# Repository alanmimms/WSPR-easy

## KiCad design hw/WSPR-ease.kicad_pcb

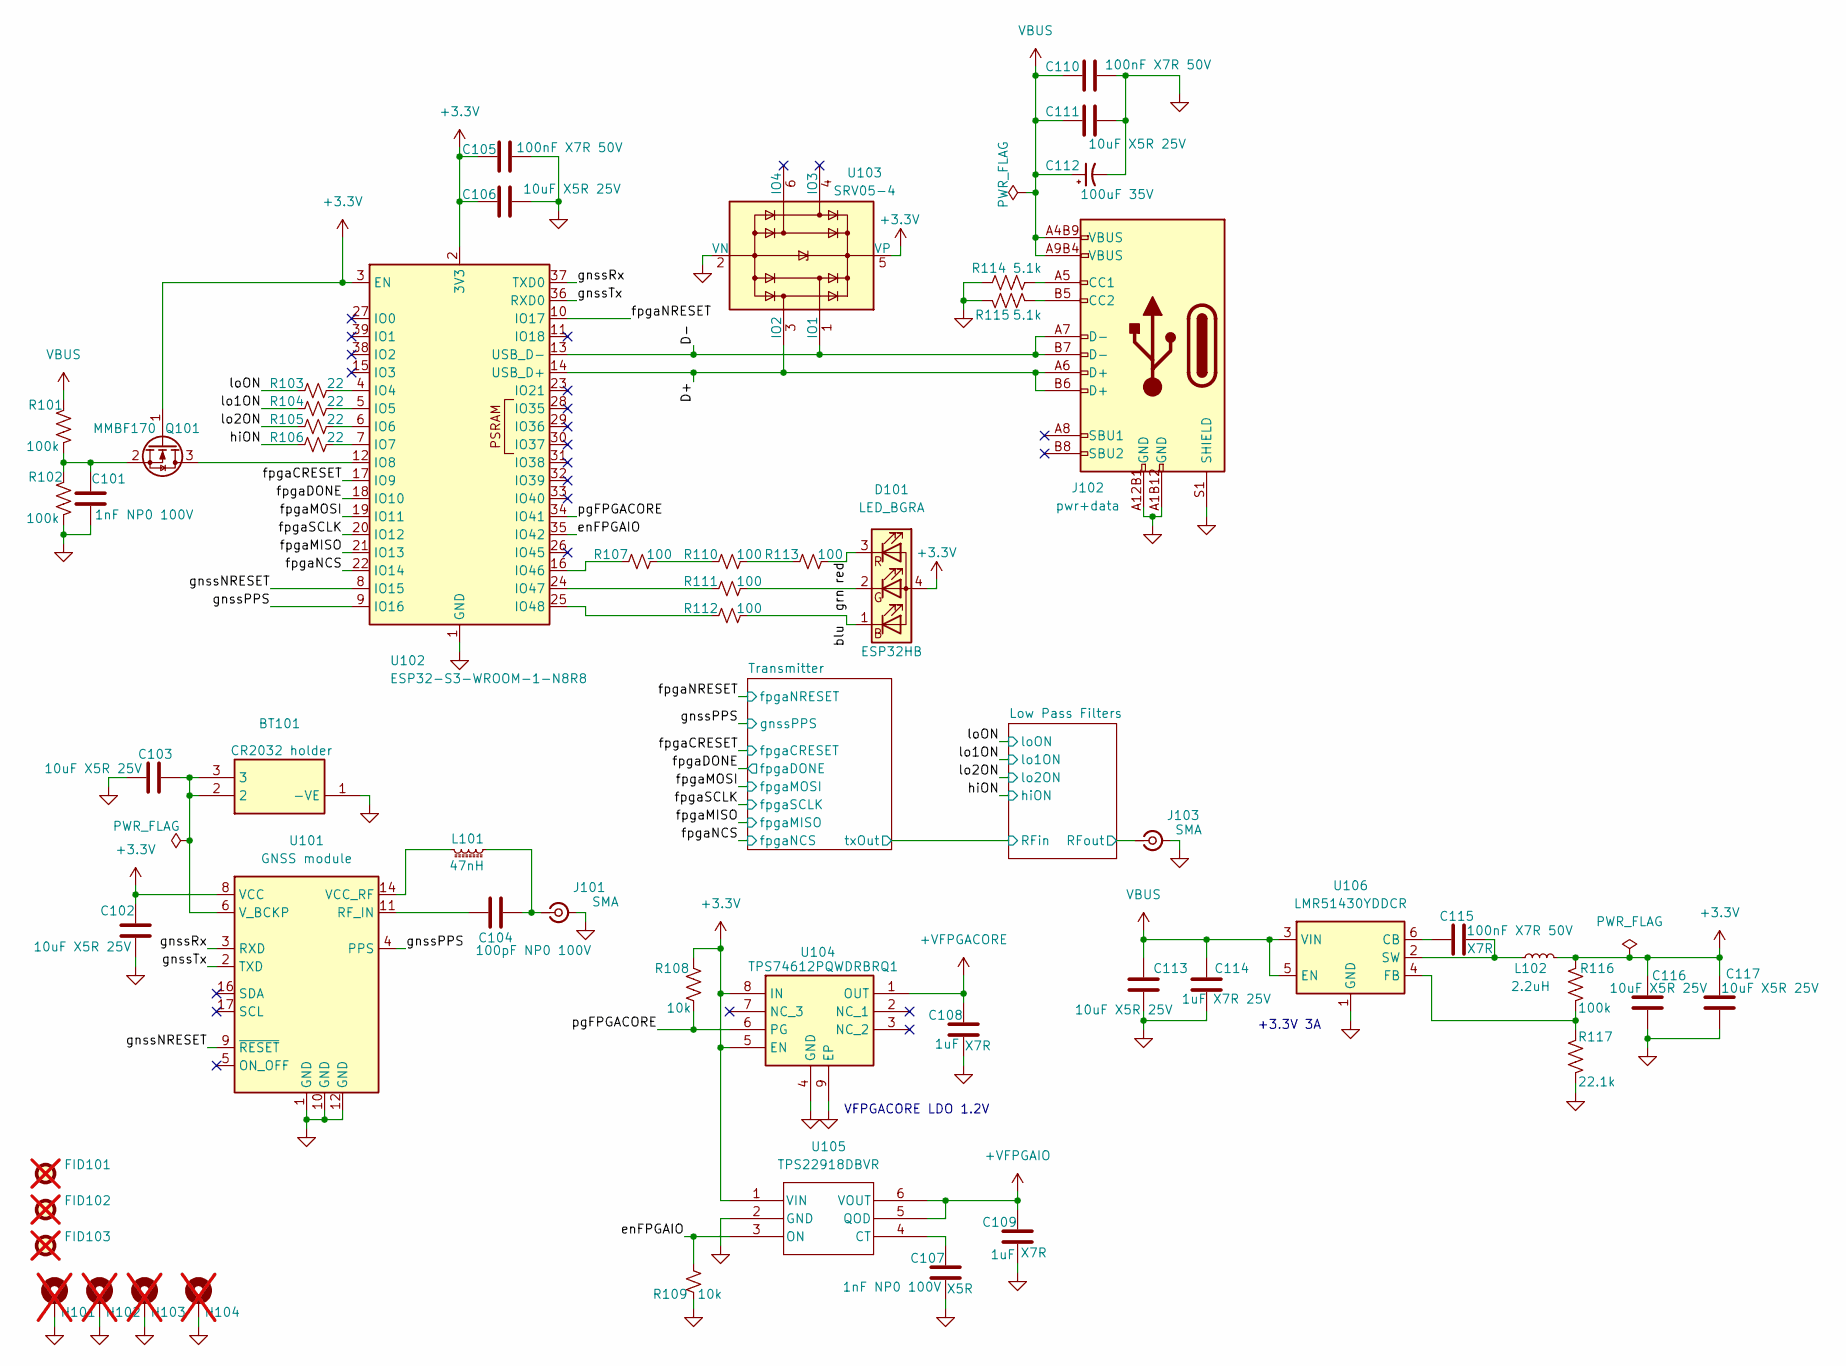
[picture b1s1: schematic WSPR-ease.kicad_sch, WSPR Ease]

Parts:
BT101: CR2032 holder; S8401-46; Mouser Part Number 855-S8401-46; LCSC C6750449
C101: 1nF NP0 100V; C_0603_1608Metric; MPN KGM15ACG2A102FT; LCSC C5182455
C102, C103, C106, C111: 10uF X5R 25V; C_0603_1608Metric; MPN CM105X5R106M25AT; LCSC C96446
C104: 100pF NP0 100V; C_0603_1608Metric; MPN KGM15ACG2A101FT; LCSC C106200
C105, C110: 100nF X7R 50V; C_0603_1608Metric; MPN KGM15BR71H104KT; LCSC C24452
C107: 1nF NP0 100V; C_0603_1608Metric; MPN KGM15ACG2A102FT; LCSC_PN C301928
C108, C109: 1uF; C_0402_1005Metric; MPN GRM155Z71A105KE1D; LCSC_PN C301928
C112: 100uF 35V; C_Elec_8x6.2; MPN MAL214297007E3; LCSC C1849748
C113: 10uF X5R 25V; C_0603_1608Metric; MPN CM105X5R106M25AT; LCSC_PN C327087
C114: 1uF X7R 25V; C_0603_1608Metric; MPN CM105X7R105K25AT; LCSC_PN C301928
C115: 100nF X7R 50V; C_0603_1608Metric; MPN KGM15BR71H104KT; LCSC_PN C24452
C116, C117: 10uF X5R 25V; C_0603_1608Metric; Manufacturer_Part_Number 81-GXT155R71E223KE1D; Mouser Part Number 963-MLAST168BB5106MT
D101: LED_BGRA; UHD111AFKAC3K23E1L3VG5ZB3Z3; MPN UHD111A-FKA-C3K23E1L3VG5ZB3Z3; Mouser_PN 941-UHD1AA3K3E3V53Z3
FID101, FID102, FID103: Fiducial; Fiducial_1mm_Mask2mm; LCSC DNP; not fitted
H101, H102, H103, H104: MountingHole_Pad; MountingHole_3.2mm_M3_ISO7380_Pad; LCSC DNP; not fitted
J101, J103: SMA; SMA_Amphenol_901-143_Horizontal; MPN SMA-J-P-H-RA-TH1; LCSC C496551
J102: pwr+data; USB_C_Receptacle_HRO_TYPE-C-31-M-12-bursted; MPN TYPE-C-31-M-12; LCSC_PN C165948
L101: 47nH; L_0603_1608Metric; MPN AIMC-0603-47NJ-T; LCSC C98076
L102: 2.2uH; L_1008_2520Metric; MPN AIML-1008HC-2R2M-T; LCSC_PN C86089
Q101: MMBF170; SOT-23; MPN MMBF170Q-13-F; LCSC C28871
R101, R102: 100k; R_0402_1005Metric; MPN CRT0402-FZ-1003GLF; LCSC C60491
R103, R104, R105, R106: 22; R_0402_1005Metric
R107, R110, R111, R112, R113: 100; R_0402_1005Metric
R108: 10k; R_0402_1005Metric; MPN CRT0402-FZ-1003GLF; LCSC_PN C728576
R109: 10k; R_0402_1005Metric
R114, R115: 5.1k; R_0402_1005Metric; MPN MCS04020C5101FE000; LCSC_PN C854378
R116: 100k; R_0402_1005Metric; MPN CRT0402-FZ-1003GLF; LCSC_PN C728576
R117: 22.1k; R_0402_1005Metric; MPN RT0402FRD0722K1L; LCSC_PN C284424
U101: GNSS module; ublox_MAX; MPN TESEO-LIV3R; LCSC C90770
U102: ESP32-S3-WROOM-1-N8R8; ESP32-S3-WROOM-1; Mouser Part Number ESP32-S3-WROOM-1-N8R8; LCSC C2913204
U103: SRV05-4; SOT-23-6; MPN SRV05-4.TCT; LCSC C2836319
U104: TPS74612PQWDRBRQ1; SON65P300X300X100-9N-D; MPN TPS74612PQWDRBRQ1; LCSC_PN C2868254
U105: TPS22918DBVR; DBV6_TEX; MPN TPS22918DBVR; LCSC_PN C131941
U106: LMR51430YDDCR; SOT-23-6; MPN LMR51430YDDCR; LCSC_PN C5185863

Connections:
+3.3V: C102.1, C105.1, C106.1, C116.1, C117.1, D101.4 (A), L102.2, Q101.1 (G), R108.2, R116.2, U101.8 (VCC), U102.2 (3V3), U102.3 (EN), U103.5 (VP), U104.5 (EN), U104.8 (IN), U105.1 (VIN); also elsewhere on the board
+VFPGACORE: C108.1, U104.1 (OUT); also elsewhere on the board
+VFPGAIO: C109.1, U105.5 (QOD), U105.6 (VOUT); also elsewhere on the board
/D+: J102.A6 (D+), J102.B6 (D+), U102.14 (USB_D+), U103.3 (IO2)
/D-: J102.A7 (D-), J102.B7 (D-), U102.13 (USB_D-), U103.1 (IO1)
/Low Pass Filters/RFout: J103.1 (In); also elsewhere on the board
/blu: D101.1 (BK), R112.2
/enFPGAIO: R109.2, U102.35 (IO42), U105.3 (ON)
/fpgaCRESET: U102.17 (IO9); also elsewhere on the board
/fpgaDONE: U102.18 (IO10); also elsewhere on the board
/fpgaMISO: U102.21 (IO13); also elsewhere on the board
/fpgaMOSI: U102.19 (IO11); also elsewhere on the board
/fpgaNCS: U102.22 (IO14); also elsewhere on the board
/fpgaNRESET: U102.10 (IO17); also elsewhere on the board
/fpgaSCLK: U102.20 (IO12); also elsewhere on the board
/gnssNRESET: U101.9 (~RESET), U102.8 (IO15)
/gnssPPS: U101.4 (PPS), U102.9 (IO16); also elsewhere on the board
/gnssRx: U101.3 (RXD), U102.37 (TXD0)
/gnssTx: U101.2 (TXD), U102.36 (RXD0)
/grn: D101.2 (GK), R111.2
/hiON: R106.1; also elsewhere on the board
/lo1ON: R104.1; also elsewhere on the board
/lo2ON: R105.1; also elsewhere on the board
/loON: R103.1; also elsewhere on the board
/pgFPGACORE: R108.1, U102.34 (IO41), U104.6 (PG)
/red: D101.3 (RK), R113.2
GND: BT101.1 (-VE), C101.2, C102.2, C103.1, C105.2, C106.2, C107.2, C108.2, C109.2, C110.2, C111.2, C112.2, C113.2, C114.2, C116.2, C117.2, H101.1, H102.1, H103.1, H104.1, J101.2 (Ext), J102.A1B12 (GND), J102.A12B1 (GND), J102.S1 (SHIELD), J103.2 (Ext), R102.2, R109.1, R114.2, R115.2, R117.1, U101.1 (GND), U101.10 (GND), U101.12 (GND), U102.1 (GND), U102.40 (GND), U102.41 (GND), U103.2 (VN), U104.4 (GND), U104.9 (EP), U105.2 (GND), U106.1 (GND); also elsewhere on the board
unnamed: C104.2, J101.1 (In), L101.2
unnamed: J102.A5 (CC1), R114.1
unnamed: J102.B5 (CC2), R115.1
unnamed: Q101.3 (D), U102.12 (IO8)
unnamed: C101.1, Q101.2 (S), R101.2, R102.1
unnamed: R107.2, R110.1
unnamed: R110.2, R113.1
unnamed: C104.1, U101.11 (RF_IN)
unnamed: L101.1, U101.14 (VCC_RF)
unnamed: BT101.2, BT101.3, C103.2, U101.6 (V_BCKP)
unnamed: R103.2, U102.4 (IO4)
unnamed: R104.2, U102.5 (IO5)
unnamed: R105.2, U102.6 (IO6)
unnamed: R106.2, U102.7 (IO7)
unnamed: R107.1, U102.16 (IO46)
unnamed: R111.1, U102.24 (IO47)
unnamed: R112.1, U102.25 (IO48)
unnamed: C107.1, U105.4 (CT)
unnamed: C115.1, U106.6 (CB)
unnamed: R116.1, R117.2, U106.4 (FB)
unnamed: C115.2, L102.1, U106.2 (SW)
VBUS: C110.1, C111.1, C112.1, C113.1, C114.1, J102.A4B9 (VBUS), J102.A9B4 (VBUS), R101.1, U106.3 (VIN), U106.5 (EN); also elsewhere on the board

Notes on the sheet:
VFPGACORE LDO 1.2V
+3.3V 3A

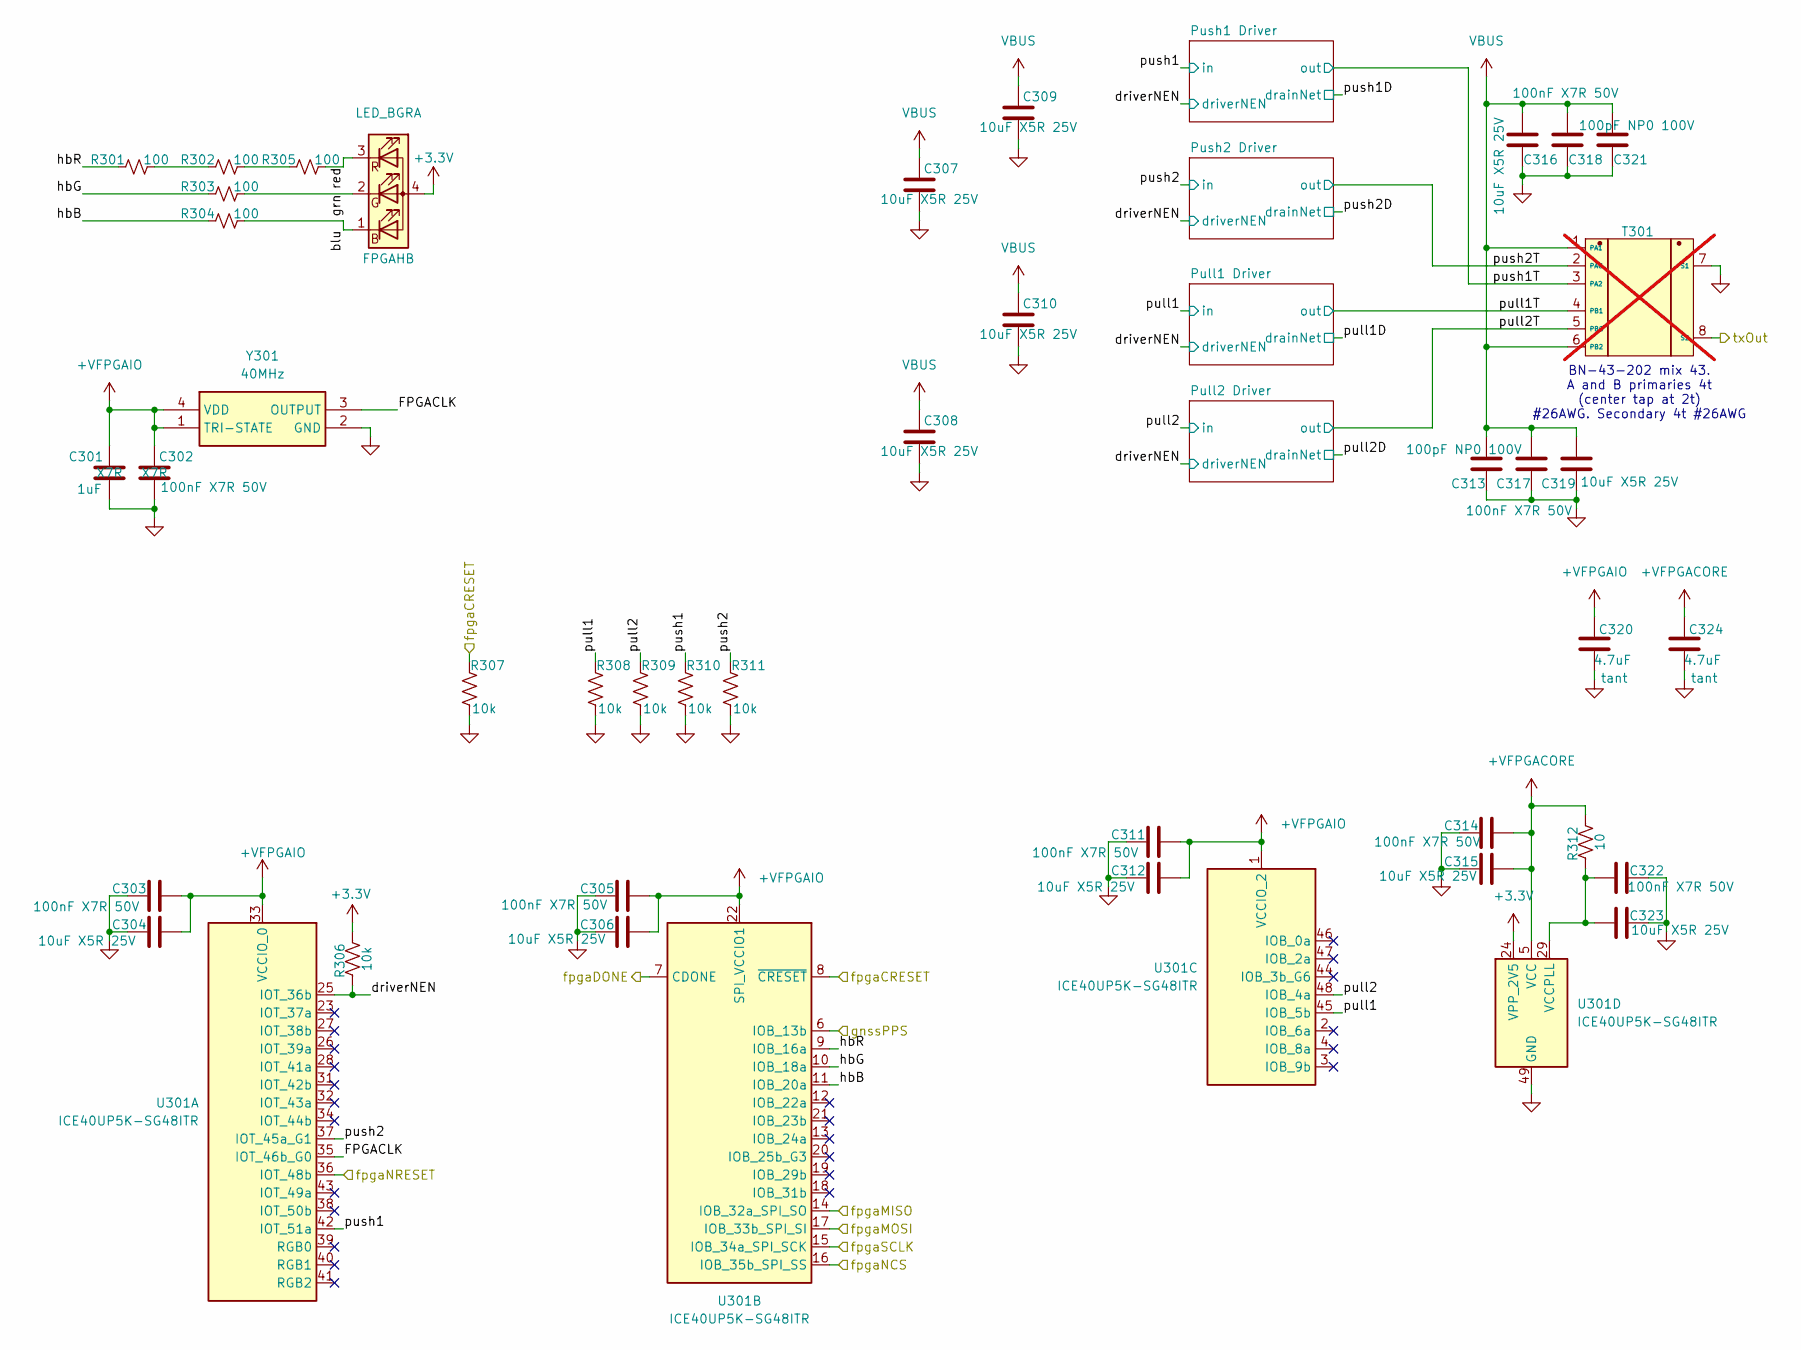
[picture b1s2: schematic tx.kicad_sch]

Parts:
C301: 1uF; C_0402_1005Metric; MPN GRM155Z71A105KE1D; LCSC_PN C301928
C302: 100nF X7R 50V; C_0603_1608Metric; MPN KGM15BR71H104KT; LCSC_PN C24452
C303, C305, C311, C314, C317, C318, C322: 100nF X7R 50V; C_0603_1608Metric; MPN KGM15BR71H104KT; LCSC C24452
C304, C306, C307, C308, C309, C310, C312, C315, C316, C319, C323: 10uF X5R 25V; C_0603_1608Metric; MPN CM105X5R106M25AT; LCSC C96446
C313, C321: 100pF NP0 100V; C_0603_1608Metric; MPN KGM15ACG2A101FT; LCSC C106200
C320, C324: 4.7uF; C_0402_1005Metric; MPN CM05X5R475M10AH; LCSC_PN C18535241
D301: LED_BGRA; UHD111AFKAC3K23E1L3VG5ZB3Z3; MPN UHD111A-FKA-C3K23E1L3VG5ZB3Z3; Mouser_PN 941-UHD1AA3K3E3V53Z3
R301, R302, R303, R304, R305: 100; R_0402_1005Metric
R306: 10k; R_0402_1005Metric; MPN MCT06030C1009FP500; LCSC C2907091
R307, R308, R309, R310, R311: 10k; R_0402_1005Metric; MPN MCS04020C1002FE000; LCSC C60490
R312: 10; R_0603_1608Metric; MPN MCT06030C1009FP500; LCSC C2907091
T301: BN-43-202_DualPri_CTSec; bn-43-202-horizontal; MPN 2843000202; LCSC C7174817; not fitted
U301: ICE40UP5K-SG48ITR; QFN-48-1EP_7x7mm_P0.5mm_EP5.6x5.6mm; MPN ICE40UP5K-SG48I; LCSC C2678152
Y301: 40MHz; ECSTXO201633400TR; MPN ECS-TXO-2016-33-400-TR; LCSC_PN C2451471

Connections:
+3.3V: D301.4 (A), R306.2, U301.24 (VPP_2V5); also elsewhere on the board
+VFPGACORE: C314.2, C315.2, C324.1, R312.2, U301.5 (VCC), U301.30 (VCC); also elsewhere on the board
+VFPGAIO: C301.1, C302.1, C303.2, C304.2, C305.2, C306.2, C311.2, C312.2, C320.1, U301.1 (VCCIO_2), U301.22 (SPI_VCCIO1), U301.33 (VCCIO_0), Y301.1 (TRI-STATE), Y301.4 (VDD); also elsewhere on the board
/Low Pass Filters/RFin: T301.8 (S2); also elsewhere on the board
/Transmitter/FPGACLK: U301.35 (IOT_46b_G0), Y301.3 (OUTPUT)
/Transmitter/blu: D301.1 (BK), R304.2
/Transmitter/driverNEN: R306.1, U301.25 (IOT_36b); also elsewhere on the board
/Transmitter/grn: D301.2 (GK), R303.2
/Transmitter/hbB: R304.1, U301.11 (IOB_20a)
/Transmitter/hbG: R303.1, U301.10 (IOB_18a)
/Transmitter/hbR: R301.1, U301.9 (IOB_16a)
/Transmitter/pull1: R308.1, U301.45 (IOB_5b); also elsewhere on the board
/Transmitter/pull1T: T301.4 (PB1); also elsewhere on the board
/Transmitter/pull2: R309.1, U301.48 (IOB_4a); also elsewhere on the board
/Transmitter/pull2T: T301.5 (PBC); also elsewhere on the board
/Transmitter/push1: R310.1, U301.42 (IOT_51a); also elsewhere on the board
/Transmitter/push1T: T301.3 (PA2); also elsewhere on the board
/Transmitter/push2: R311.1, U301.37 (IOT_45a_G1); also elsewhere on the board
/Transmitter/push2T: T301.2 (PAC); also elsewhere on the board
/Transmitter/red: D301.3 (RK), R305.2
/fpgaCRESET: R307.1, U301.8 (~CRESET); also elsewhere on the board
/fpgaDONE: U301.7 (CDONE); also elsewhere on the board
/fpgaMISO: U301.14 (IOB_32a_SPI_SO); also elsewhere on the board
/fpgaMOSI: U301.17 (IOB_33b_SPI_SI); also elsewhere on the board
/fpgaNCS: U301.16 (IOB_35b_SPI_SS); also elsewhere on the board
/fpgaNRESET: U301.36 (IOT_48b); also elsewhere on the board
/fpgaSCLK: U301.15 (IOB_34a_SPI_SCK); also elsewhere on the board
/gnssPPS: U301.6 (IOB_13b); also elsewhere on the board
GND: C301.2, C302.2, C303.1, C304.1, C305.1, C306.1, C307.1, C308.1, C309.1, C310.1, C311.1, C312.1, C313.1, C314.1, C315.1, C316.1, C317.1, C318.1, C319.1, C320.2, C321.1, C322.1, C323.1, C324.2, R307.2, R308.2, R309.2, R310.2, R311.2, T301.7 (S1), U301.49 (GND), Y301.2 (GND); also elsewhere on the board
unnamed: R301.2, R302.1
unnamed: R302.2, R305.1
unnamed: C322.2, C323.2, R312.1, U301.29 (VCCPLL)
VBUS: C307.2, C308.2, C309.2, C310.2, C313.2, C316.2, C317.2, C318.2, C319.2, C321.2, T301.1 (PA1), T301.6 (PB2); also elsewhere on the board

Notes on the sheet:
BN-43-202 mix 43. A and B primaries 4t (center tap at 2t) #26AWG. Secondary 4t #26AWG

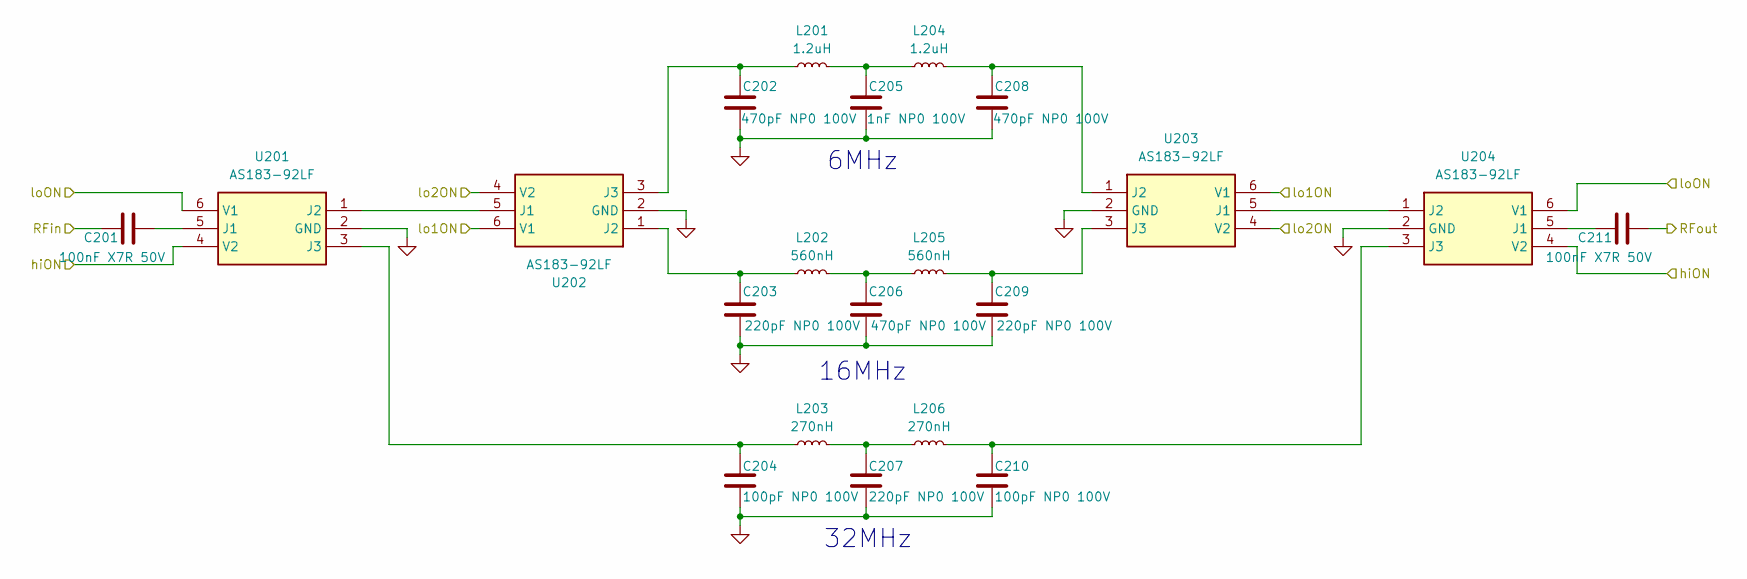
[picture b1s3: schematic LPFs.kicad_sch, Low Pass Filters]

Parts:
C201, C211: 100nF X7R 50V; C_0603_1608Metric; MPN KGM15BR71H104KT; LCSC C24452
C202, C206, C208: 470pF NP0 100V; C_0603_1608Metric; MPN GCM1885C2A471FA6D; LCSC C106259
C203, C207, C209: 220pF NP0 100V; C_0603_1608Metric; MPN GCM1885C2A221FA6D; LCSC C107001
C204, C210: 100pF NP0 100V; C_0603_1608Metric; MPN KGM15ACG2A101FT; LCSC C106200
C205: 1nF NP0 100V; C_0603_1608Metric; MPN KGM15ACG2A102FT; LCSC C5182455
L201, L204: 1.2uH; L_1008_2520Metric; MPN CW252016-1R2J; LCSC C2044063
L202, L205: 560nH; L_1008_2520Metric; MPN LQW2UASR56G00L; LCSC C6364717
L203, L206: 270nH; L_0805_2012Metric; MPN CW252016-R27J; LCSC C404430
U201, U202, U203, U204: AS183-92LF; SOT65P220X110-6N; Mouser Part Number 873-AS183-92LF

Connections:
/Low Pass Filters/RFin: C201.1; also elsewhere on the board
/Low Pass Filters/RFout: C211.2; also elsewhere on the board
/hiON: U201.4 (V2), U204.4 (V2); also elsewhere on the board
/lo1ON: U202.6 (V1), U203.6 (V1); also elsewhere on the board
/lo2ON: U202.4 (V2), U203.4 (V2); also elsewhere on the board
/loON: U201.6 (V1), U204.6 (V1); also elsewhere on the board
GND: C202.2, C203.2, C204.2, C205.2, C206.2, C207.2, C208.2, C209.2, C210.2, U201.2 (GND), U202.2 (GND), U203.2 (GND), U204.2 (GND); also elsewhere on the board
unnamed: C205.1, L201.2, L204.1
unnamed: C206.1, L202.2, L205.1
unnamed: C207.1, L203.2, L206.1
unnamed: C201.2, U201.5 (J1)
unnamed: U201.1 (J2), U202.5 (J1)
unnamed: C204.1, L203.1, U201.3 (J3)
unnamed: C203.1, L202.1, U202.1 (J2)
unnamed: C202.1, L201.1, U202.3 (J3)
unnamed: U203.5 (J1), U204.1 (J2)
unnamed: C208.1, L204.2, U203.1 (J2)
unnamed: C209.1, L205.2, U203.3 (J3)
unnamed: C211.1, U204.5 (J1)
unnamed: C210.1, L206.2, U204.3 (J3)

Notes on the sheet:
6MHz
32MHz
16MHz

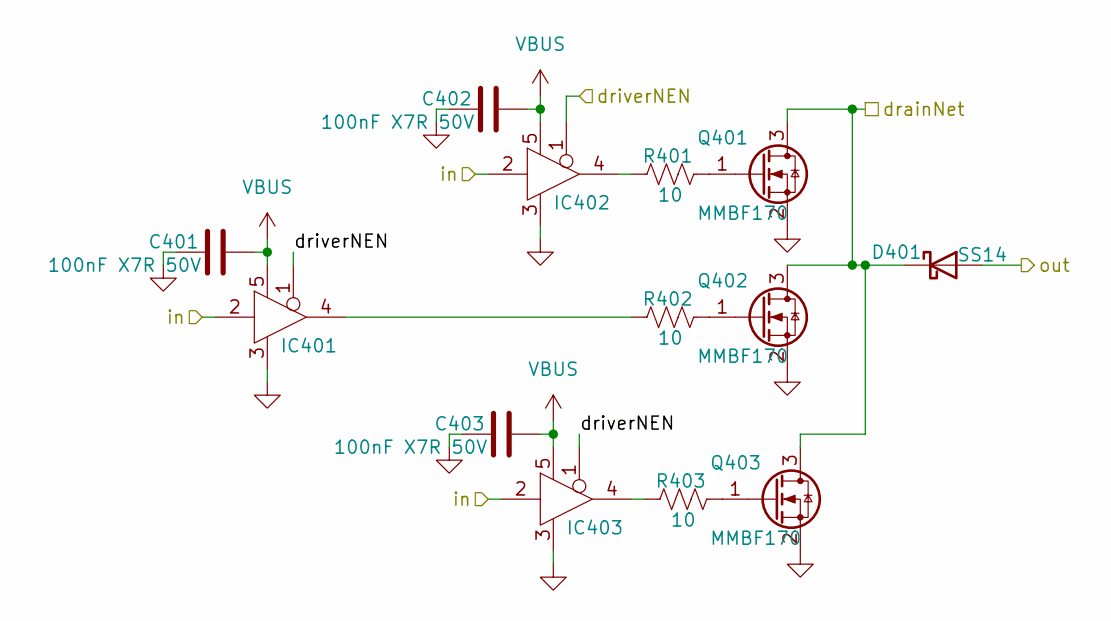
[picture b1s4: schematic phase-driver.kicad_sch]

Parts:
C401, C402, C403: 100nF X7R 50V; C_0603_1608Metric; MPN KGM15BR71H104KT; LCSC C24452
D401: SS14; D_SMA; MPN SS14; LCSC C83852
IC401, IC402, IC403: SN74AHCT1G125DRLR; SOTFL50P160X60-5N; Mouser Part Number 595-SN74AHCT1G125DRL
Q401, Q402, Q403: MMBF170; SOT-23; MPN MMBF170Q-13-F; LCSC C28871
R401, R402, R403: 10; R_0603_1608Metric; MPN MCT06030C1009FP500; LCSC C2907091

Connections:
/Transmitter/driverNEN: IC401.1 (~OE), IC402.1 (~OE), IC403.1 (~OE); also elsewhere on the board
/Transmitter/push1: IC401.2 (A), IC402.2 (A), IC403.2 (A); also elsewhere on the board
/Transmitter/push1D: D401.1 (K), Q401.3 (D), Q402.3 (D), Q403.3 (D)
/Transmitter/push1T: D401.2 (A); also elsewhere on the board
GND: C401.1, C402.1, C403.1, IC401.3 (GND), IC402.3 (GND), IC403.3 (GND), Q401.2 (S), Q402.2 (S), Q403.2 (S); also elsewhere on the board
unnamed: IC401.4 (Y), R402.1
unnamed: IC402.4 (Y), R401.1
unnamed: IC403.4 (Y), R403.1
unnamed: Q401.1 (G), R401.2
unnamed: Q402.1 (G), R402.2
unnamed: Q403.1 (G), R403.2
VBUS: C401.2, C402.2, C403.2, IC401.5 (VCC), IC402.5 (VCC), IC403.5 (VCC); also elsewhere on the board

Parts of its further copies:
C501, C502, C503, C601, C602, C603, C701, C702, C703: 100nF X7R 50V; C_0603_1608Metric; MPN KGM15BR71H104KT; LCSC C24452
D501, D601, D701: SS14; D_SMA; MPN SS14; LCSC C83852
IC501, IC502, IC503, IC601, IC602, IC603, IC701, IC702, IC703: SN74AHCT1G125DRLR; SOTFL50P160X60-5N; Mouser Part Number 595-SN74AHCT1G125DRL
Q501, Q502, Q503, Q601, Q602, Q603, Q701, Q702, Q703: MMBF170; SOT-23; MPN MMBF170Q-13-F; LCSC C28871
R501, R502, R503, R601, R602, R603, R701, R702, R703: 10; R_0603_1608Metric; MPN MCT06030C1009FP500; LCSC C2907091

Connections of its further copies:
/Transmitter/driverNEN: IC501.1 (~OE), IC502.1 (~OE), IC503.1 (~OE), IC601.1 (~OE), IC602.1 (~OE), IC603.1 (~OE), IC701.1 (~OE), IC702.1 (~OE), IC703.1 (~OE); also elsewhere on the board
/Transmitter/pull1: IC601.2 (A), IC602.2 (A), IC603.2 (A); also elsewhere on the board
/Transmitter/pull1D: D601.1 (K), Q601.3 (D), Q602.3 (D), Q603.3 (D)
/Transmitter/pull1T: D601.2 (A); also elsewhere on the board
/Transmitter/pull2: IC701.2 (A), IC702.2 (A), IC703.2 (A); also elsewhere on the board
/Transmitter/pull2D: D701.1 (K), Q701.3 (D), Q702.3 (D), Q703.3 (D)
/Transmitter/pull2T: D701.2 (A); also elsewhere on the board
/Transmitter/push2: IC501.2 (A), IC502.2 (A), IC503.2 (A); also elsewhere on the board
/Transmitter/push2D: D501.1 (K), Q501.3 (D), Q502.3 (D), Q503.3 (D)
/Transmitter/push2T: D501.2 (A); also elsewhere on the board
GND: C501.1, C502.1, C503.1, C601.1, C602.1, C603.1, C701.1, C702.1, C703.1, IC501.3 (GND), IC502.3 (GND), IC503.3 (GND), IC601.3 (GND), IC602.3 (GND), IC603.3 (GND), IC701.3 (GND), IC702.3 (GND), IC703.3 (GND), Q501.2 (S), Q502.2 (S), Q503.2 (S), Q601.2 (S), Q602.2 (S), Q603.2 (S), Q701.2 (S), Q702.2 (S), Q703.2 (S); also elsewhere on the board
unnamed: IC501.4 (Y), R502.1
unnamed: IC502.4 (Y), R501.1
unnamed: IC503.4 (Y), R503.1
unnamed: IC601.4 (Y), R602.1
unnamed: IC602.4 (Y), R601.1
unnamed: IC603.4 (Y), R603.1
unnamed: IC701.4 (Y), R702.1
unnamed: IC702.4 (Y), R701.1
unnamed: IC703.4 (Y), R703.1
unnamed: Q501.1 (G), R501.2
unnamed: Q502.1 (G), R502.2
unnamed: Q503.1 (G), R503.2
unnamed: Q601.1 (G), R601.2
unnamed: Q602.1 (G), R602.2
unnamed: Q603.1 (G), R603.2
unnamed: Q701.1 (G), R701.2
unnamed: Q702.1 (G), R702.2
unnamed: Q703.1 (G), R703.2
VBUS: C501.2, C502.2, C503.2, C601.2, C602.2, C603.2, C701.2, C702.2, C703.2, IC501.5 (VCC), IC502.5 (VCC), IC503.5 (VCC), IC601.5 (VCC), IC602.5 (VCC), IC603.5 (VCC), IC701.5 (VCC), IC702.5 (VCC), IC703.5 (VCC); also elsewhere on the board

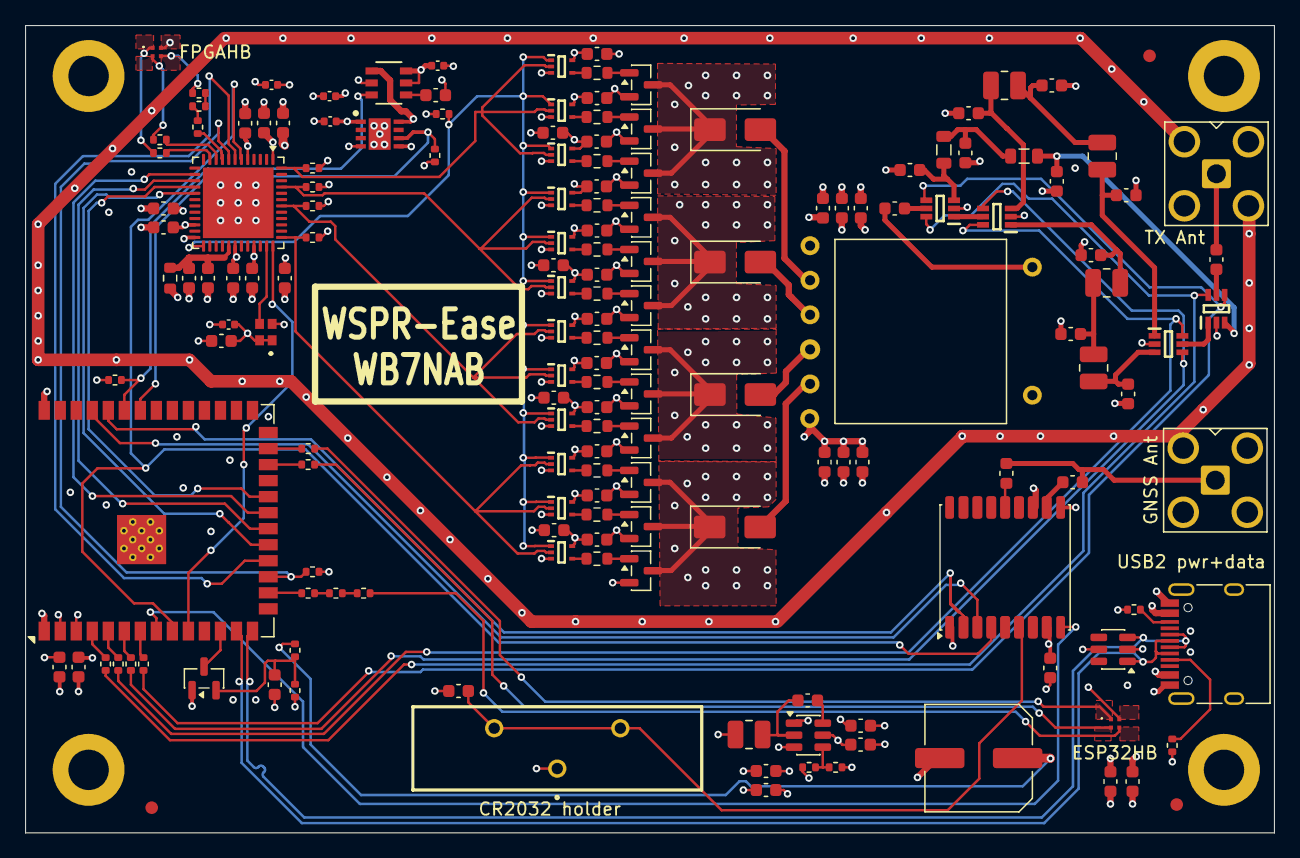
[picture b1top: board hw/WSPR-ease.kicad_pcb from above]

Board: 4 copper layers, 99.0 x 64.0 mm, 168 parts (0 on the bottom side), 110 nets.

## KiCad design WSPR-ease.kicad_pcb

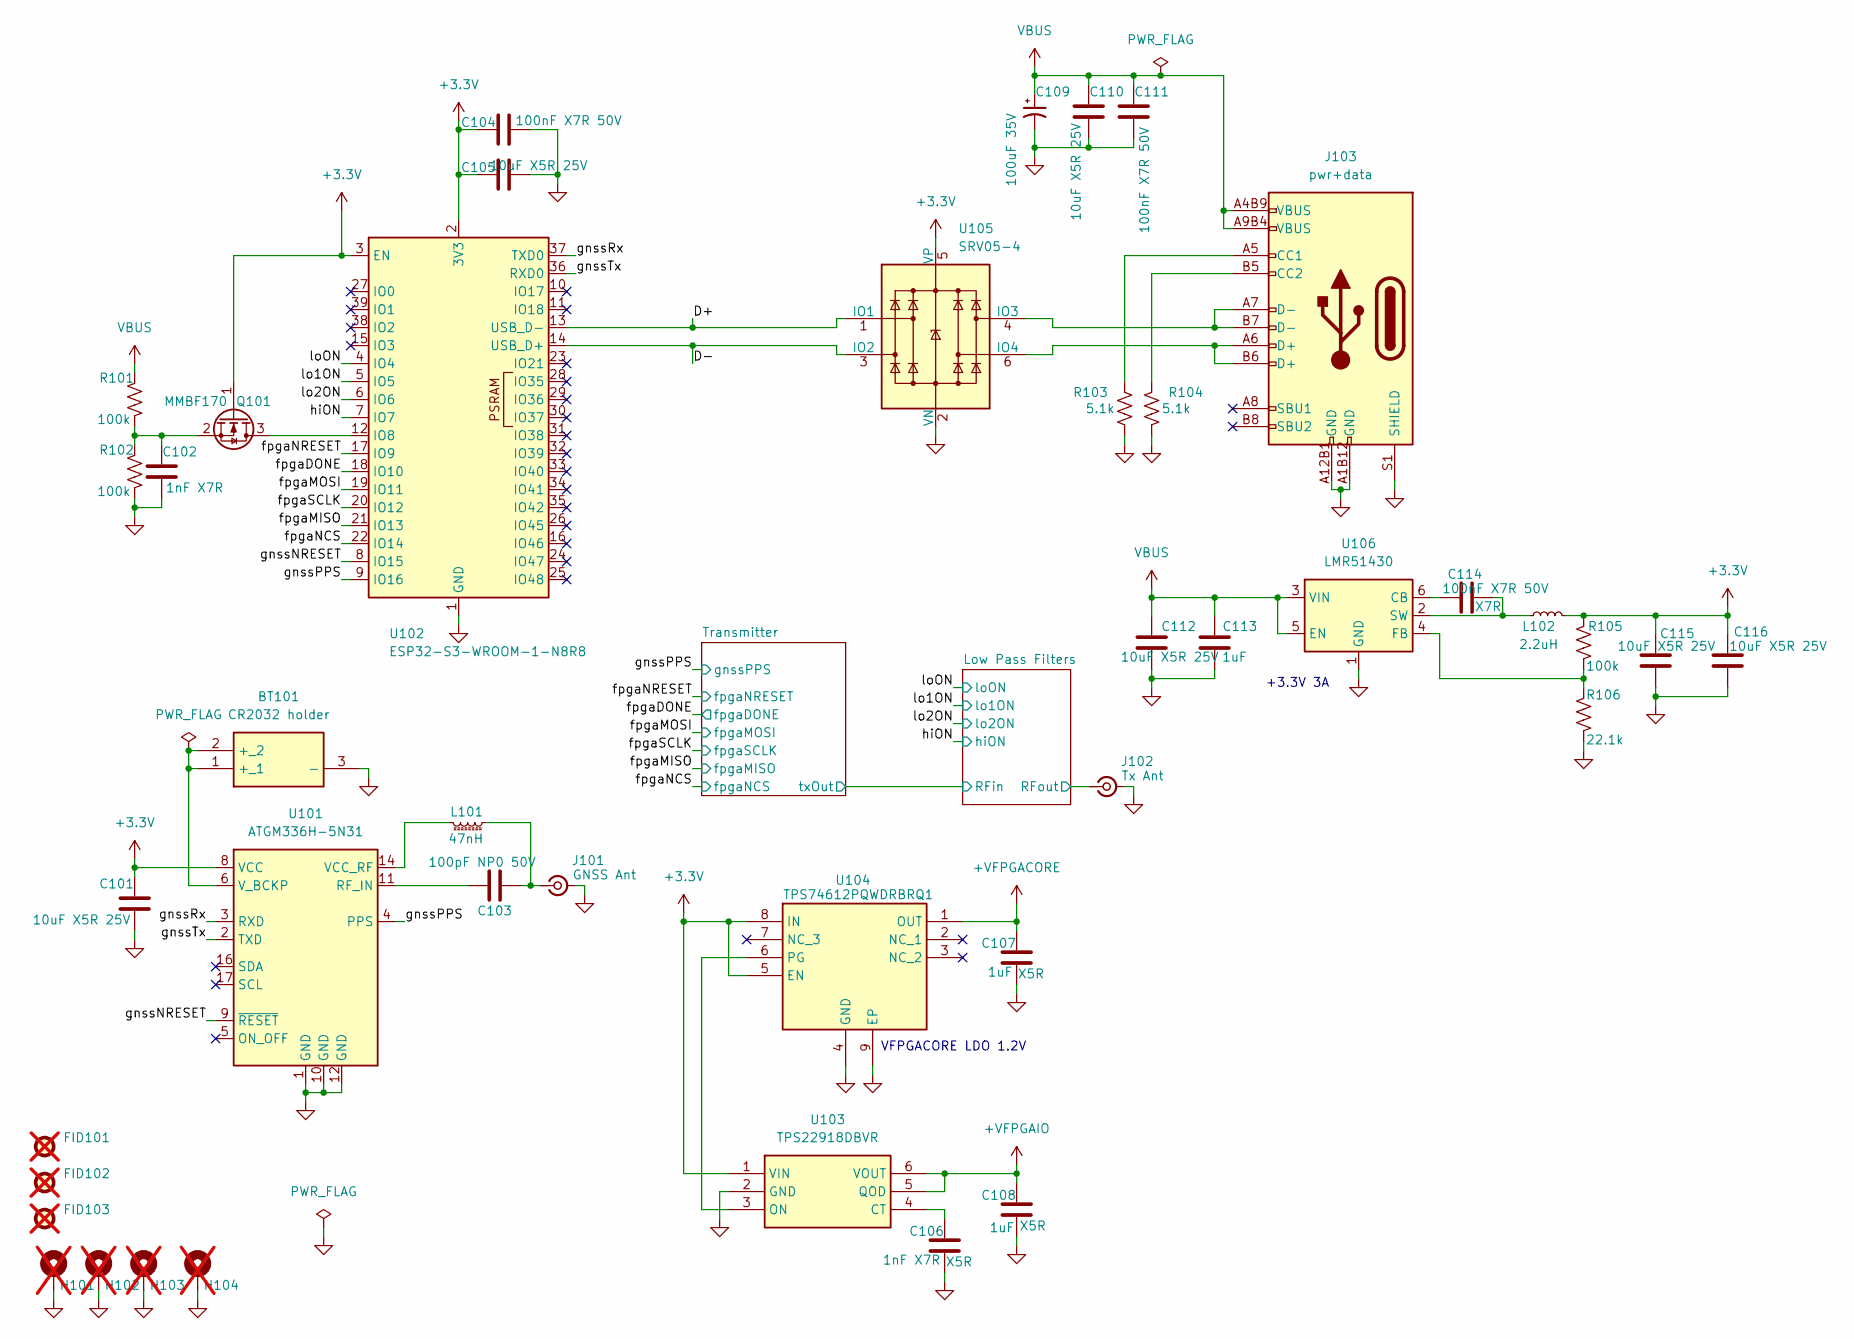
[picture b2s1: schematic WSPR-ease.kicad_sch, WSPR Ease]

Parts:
BT101: CR2032 holder; BATHLD014THM; Mouser Part Number 712-BAT-HLD-014-THM; LCSC C31226699
C101, C105, C110: 10uF X5R 25V; C_0603_1608Metric; LCSC C96446
C102: 1nF X7R; C_0402_1005Metric; LCSC C106205
C103: 100pF NP0 50V; C_0402_1005Metric; LCSC C106200
C104, C111: 100nF X7R 50V; C_0603_1608Metric; LCSC C24452
C106: 1nF X7R; C_0402_1005Metric; Mouser_PN 81-GRM155R61E105KE1D; LCSC_PN C301928
C107, C108, C113: 1uF; C_0402_1005Metric; Mouser_PN 81-GRM155R61E105KE1D; LCSC_PN C301928
C109: 100uF 35V; CAPAE850X1050N; Mouser Part Number MAL215097011E3; LCSC C1849748
C112: 10uF X5R 25V; C_0603_1608Metric; Mouser_PN 963-MLAST168BB5106MT; LCSC_PN C327087
C114: 100nF X7R 50V; C_0603_1608Metric; Mouser_PN 80-C0805F104K1RAUTO; LCSC_PN C24452
C115, C116: 10uF X5R 25V; C_0603_1608Metric; Manufacturer_Part_Number 81-GXT155R71E223KE1D; Mouser Part Number 963-MLAST168BB5106MT
FID101, FID102, FID103: Fiducial; Fiducial_1mm_Mask2mm; LCSC DNP; not fitted
H101, H102, H103, H104: MountingHole_Pad; MountingHole_3.2mm_M3_ISO7380_Pad; LCSC DNP; not fitted
J101: GNSS Ant; SMA_BAT_Wireless_BWSMA-KWE-Z001; LCSC C496551
J102: Tx Ant; SMA_BAT_Wireless_BWSMA-KWE-Z001; LCSC C496551
J103: pwr+data; USB_C_Receptacle_HRO_TYPE-C-31-M-12-bursted; MPN TYPE-C-31-M-12; LCSC_PN C165948
L101: 47nH; L_0603_1608Metric; LCSC C98076
L102: 2.2uH; L_0805_2012Metric; Part Number LQM21PN2R2NGCD; LCSC_PN C86089
Q101: MMBF170; SOT-23; LCSC C28871
R101, R102: 100k; R_0402_1005Metric; LCSC C60491
R103, R104: 5.1k; R_0402_1005Metric; LCSC_PN C854378
R105: 100k; R_0402_1005Metric; LCSC_PN C728576
R106: 22.1k; R_0402_1005Metric; LCSC_PN C284424
U101: ATGM336H-5N31; ublox_MAX; MPN ATGM336H-5N31; LCSC C90770
U102: ESP32-S3-WROOM-1-N8R8; ESP32-S3-WROOM-1; Mouser Part Number ESP32-S3-WROOM-1-N8R8; LCSC C2913204
U103: TPS22918DBVR; SOT-23-6; MPN TPS22918DBVR; LCSC_PN C131941
U104: TPS74612PQWDRBRQ1; SON65P300X300X100-9N-D; MPN TPS74612PQWDRBRQ1; LCSC_PN C2868254
U105: SRV05-4; SOT-23-6; LCSC C2836319
U106: LMR51430; SOT-23-6; LCSC_PN C5185863

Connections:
+3.3V: C101.1, C104.1, C105.1, C115.1, C116.1, L102.2, Q101.1 (G), R105.2, U101.8 (VCC), U102.2 (3V3), U102.3 (EN), U103.1 (VIN), U104.5 (EN), U104.8 (IN), U105.5 (VP); also elsewhere on the board
+VFPGACORE: C107.1, U104.1 (OUT); also elsewhere on the board
+VFPGAIO: C108.1, U103.5 (QOD), U103.6 (VOUT); also elsewhere on the board
/D+: U102.13 (USB_D-), U105.1 (IO1)
/D-: U102.14 (USB_D+), U105.3 (IO2)
/Low Pass Filters/RFout: J102.1 (In); also elsewhere on the board
/fpgaDONE: U102.18 (IO10); also elsewhere on the board
/fpgaMISO: U102.21 (IO13); also elsewhere on the board
/fpgaMOSI: U102.19 (IO11); also elsewhere on the board
/fpgaNCS: U102.22 (IO14); also elsewhere on the board
/fpgaNRESET: U102.17 (IO9); also elsewhere on the board
/fpgaSCLK: U102.20 (IO12); also elsewhere on the board
/gnssNRESET: U101.9 (~RESET), U102.8 (IO15)
/gnssPPS: U101.4 (PPS), U102.9 (IO16); also elsewhere on the board
/gnssRx: U101.3 (RXD), U102.37 (TXD0)
/gnssTx: U101.2 (TXD), U102.36 (RXD0)
/hiON: U102.7 (IO7); also elsewhere on the board
/lo1ON: U102.5 (IO5); also elsewhere on the board
/lo2ON: U102.6 (IO6); also elsewhere on the board
/loON: U102.4 (IO4); also elsewhere on the board
GND: BT101.3 (-), C101.2, C102.2, C104.2, C105.2, C106.2, C107.2, C108.2, C109.2, C110.2, C111.2, C112.2, C113.2, C115.2, C116.2, H101.1, H102.1, H103.1, H104.1, J101.2 (Ext), J102.2 (Ext), J103.A1B12 (GND), J103.A12B1 (GND), J103.S1 (SHIELD), R102.2, R103.2, R104.2, R106.1, U101.1 (GND), U101.10 (GND), U101.12 (GND), U102.1 (GND), U102.40 (GND), U102.41 (GND), U103.2 (GND), U104.4 (GND), U104.9 (EP), U105.2 (VN), U106.1 (GND); also elsewhere on the board
unnamed: BT101.1 (+_1), BT101.2 (+_2), U101.6 (V_BCKP)
unnamed: C103.2, J101.1 (In), L101.2
unnamed: J103.A5 (CC1), R103.1
unnamed: J103.B5 (CC2), R104.1
unnamed: Q101.3 (D), U102.12 (IO8)
unnamed: C102.1, Q101.2 (S), R101.2, R102.1
unnamed: C103.1, U101.11 (RF_IN)
unnamed: L101.1, U101.14 (VCC_RF)
unnamed: C106.1, U103.4 (CT)
unnamed: U103.3 (ON), U104.6 (PG)
unnamed: J103.A7 (D-), J103.B7 (D-), U105.4 (IO3)
unnamed: J103.A6 (D+), J103.B6 (D+), U105.6 (IO4)
unnamed: C114.1, U106.6 (CB)
unnamed: R105.1, R106.2, U106.4 (FB)
unnamed: C114.2, L102.1, U106.2 (SW)
VBUS: C109.1, C110.1, C111.1, C112.1, C113.1, J103.A4B9 (VBUS), J103.A9B4 (VBUS), R101.1, U106.3 (VIN), U106.5 (EN); also elsewhere on the board

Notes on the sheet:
VFPGACORE LDO 1.2V
+3.3V 3A
